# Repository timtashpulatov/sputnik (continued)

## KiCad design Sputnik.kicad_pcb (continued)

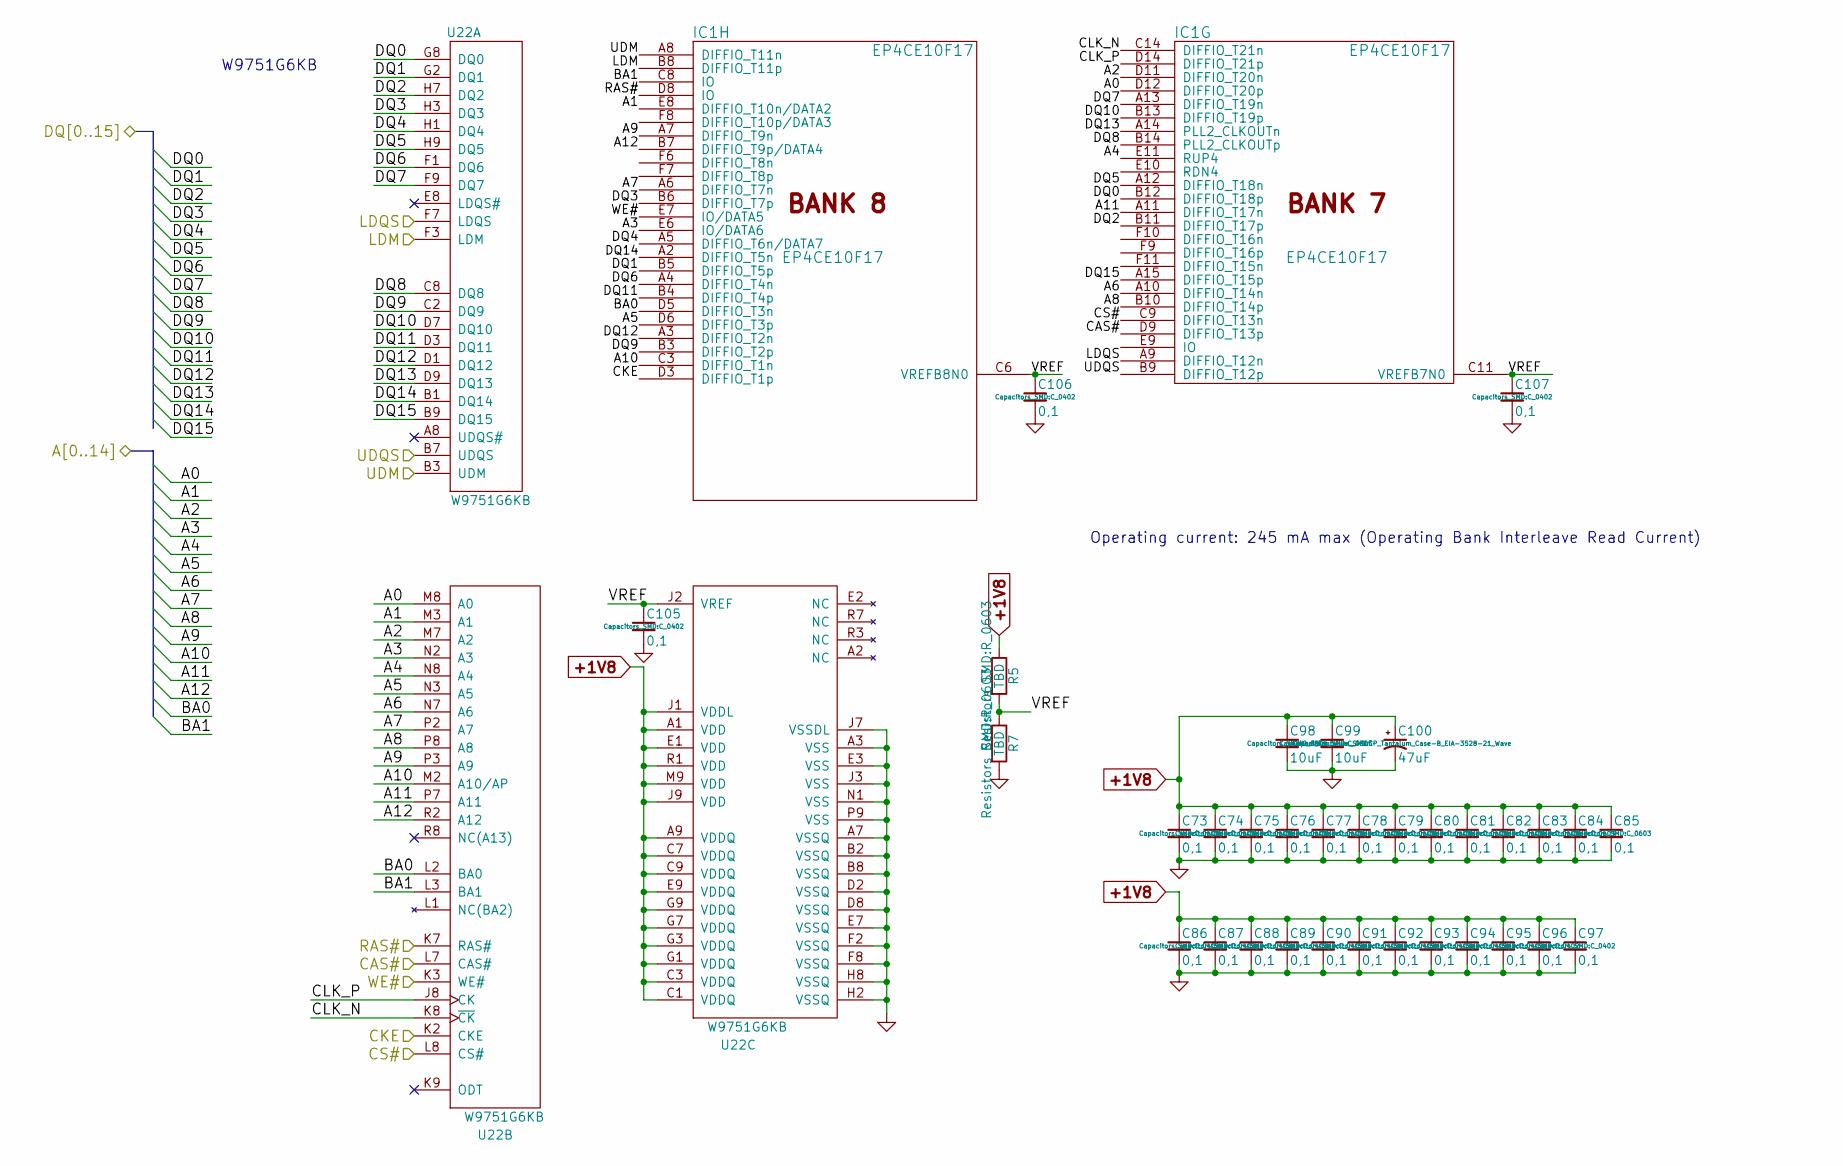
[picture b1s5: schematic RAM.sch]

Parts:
C73, C74, C75, C76, C77, C78, C79, C80, C81, C82, C83, C84, C85: 0,1; C_0603
C86, C87, C88, C89, C90, C91, C92, C93, C94, C95, C96, C97, C105, C106, C107: 0,1; C_0402
C98, C99: 10uF; C_0805
C100: 47uF; CP_Tantalum_Case-B_EIA-3528-21_Wave
IC1: EP4CE10F17; BGA-256-NSMD
R5, R7: TBD; R_0603
U22: W9751G6KB; WBGA-84

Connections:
+1V8: C73.1, C74.1, C75.1, C76.1, C77.1, C78.1, C79.1, C80.1, C81.1, C82.1, C83.1, C84.1, C85.1, C86.1, C87.1, C88.1, C89.1, C90.1, C91.1, C92.1, C93.1, C94.1, C95.1, C96.1, C97.1, C98.1, C99.1, C100.1, R5.1, U22.A1 (VDD), U22.A9 (VDDQ), U22.C1 (VDDQ), U22.C3 (VDDQ), U22.C7 (VDDQ), U22.C9 (VDDQ), U22.E1 (VDD), U22.E9 (VDDQ), U22.G1 (VDDQ), U22.G3 (VDDQ), U22.G7 (VDDQ), U22.G9 (VDDQ), U22.J1 (VDDL), U22.J9 (VDD), U22.M9 (VDD), U22.R1 (VDD); also elsewhere on the board
/RAM/A0: IC1.D12 (DIFFIO_T20p), U22.M8 (A0)
/RAM/A1: IC1.E8 (DIFFIO_T10n/DATA2), U22.M3 (A1)
/RAM/A2: IC1.D11 (DIFFIO_T20n), U22.M7 (A2)
/RAM/A3: IC1.E6 (IO/DATA6), U22.N2 (A3)
/RAM/A4: IC1.E11 (RUP4), U22.N8 (A4)
/RAM/A5: IC1.D6 (DIFFIO_T3p), U22.N3 (A5)
/RAM/A6: IC1.A10 (DIFFIO_T14n), U22.N7 (A6)
/RAM/A7: IC1.A6 (DIFFIO_T7n), U22.P2 (A7)
/RAM/A8: IC1.B10 (DIFFIO_T14p), U22.P8 (A8)
/RAM/A9: IC1.A7 (DIFFIO_T9n), U22.P3 (A9)
/RAM/A10: IC1.C3 (DIFFIO_T1n), U22.M2 (A10/AP)
/RAM/A11: IC1.A11 (DIFFIO_T17n), U22.P7 (A11)
/RAM/A12: IC1.B7 (DIFFIO_T9p/DATA4), U22.R2 (A12)
/RAM/BA0: IC1.D5 (DIFFIO_T3n), U22.L2 (BA0)
/RAM/BA1: IC1.C8 (IO), U22.L3 (BA1)
/RAM/CAS#: IC1.D9 (DIFFIO_T13p), U22.L7 (CAS#)
/RAM/CKE: IC1.D3 (DIFFIO_T1p), U22.K2 (CKE)
/RAM/CLK_N: IC1.C14 (DIFFIO_T21n), U22.K8 (~CK)
/RAM/CLK_P: IC1.D14 (DIFFIO_T21p), U22.J8 (CK)
/RAM/CS#: IC1.C9 (DIFFIO_T13n), U22.L8 (CS#)
/RAM/DQ0: IC1.B12 (DIFFIO_T18p), U22.G8 (DQ0)
/RAM/DQ1: IC1.B5 (DIFFIO_T5p), U22.G2 (DQ1)
/RAM/DQ2: IC1.B11 (DIFFIO_T17p), U22.H7 (DQ2)
/RAM/DQ3: IC1.B6 (DIFFIO_T7p), U22.H3 (DQ3)
/RAM/DQ4: IC1.A5 (DIFFIO_T6n/DATA7), U22.H1 (DQ4)
/RAM/DQ5: IC1.A12 (DIFFIO_T18n), U22.H9 (DQ5)
/RAM/DQ6: IC1.A4 (DIFFIO_T4n), U22.F1 (DQ6)
/RAM/DQ7: IC1.A13 (DIFFIO_T19n), U22.F9 (DQ7)
/RAM/DQ8: IC1.B14 (PLL2_CLKOUTp), U22.C8 (DQ8)
/RAM/DQ9: IC1.B3 (DIFFIO_T2p), U22.C2 (DQ9)
/RAM/DQ10: IC1.B13 (DIFFIO_T19p), U22.D7 (DQ10)
/RAM/DQ11: IC1.B4 (DIFFIO_T4p), U22.D3 (DQ11)
/RAM/DQ12: IC1.A3 (DIFFIO_T2n), U22.D1 (DQ12)
/RAM/DQ13: IC1.A14 (PLL2_CLKOUTn), U22.D9 (DQ13)
/RAM/DQ14: IC1.A2 (DIFFIO_T5n), U22.B1 (DQ14)
/RAM/DQ15: IC1.A15 (DIFFIO_T15p), U22.B9 (DQ15)
/RAM/LDM: IC1.B8 (DIFFIO_T11p), U22.F3 (LDM)
/RAM/LDQS: IC1.A9 (DIFFIO_T12n), U22.F7 (LDQS)
/RAM/RAS#: IC1.D8 (IO), U22.K7 (RAS#)
/RAM/UDM: IC1.A8 (DIFFIO_T11n), U22.B3 (UDM)
/RAM/UDQS: IC1.B9 (DIFFIO_T12p), U22.B7 (UDQS)
/RAM/VREF: C105.1, C106.1, C107.1, IC1.C6 (VREFB8N0), IC1.C11 (VREFB7N0), R5.2, R7.1, U22.J2 (VREF)
/RAM/WE#: IC1.E7 (IO/DATA5), U22.K3 (WE#)
GND: C73.2, C74.2, C75.2, C76.2, C77.2, C78.2, C79.2, C80.2, C81.2, C82.2, C83.2, C84.2, C85.2, C86.2, C87.2, C88.2, C89.2, C90.2, C91.2, C92.2, C93.2, C94.2, C95.2, C96.2, C97.2, C98.2, C99.2, C100.2, C105.2, C106.2, C107.2, R7.2, U22.A3 (VSS), U22.A7 (VSSQ), U22.B2 (VSSQ), U22.B8 (VSSQ), U22.D2 (VSSQ), U22.D8 (VSSQ), U22.E3 (VSS), U22.E7 (VSSQ), U22.F2 (VSSQ), U22.F8 (VSSQ), U22.H2 (VSSQ), U22.H8 (VSSQ), U22.J3 (VSS), U22.J7 (VSSDL), U22.N1 (VSS), U22.P9 (VSS); also elsewhere on the board

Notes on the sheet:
W9751G6KB
Operating current: 245 mA max (Operating Bank Interleave Read Current)

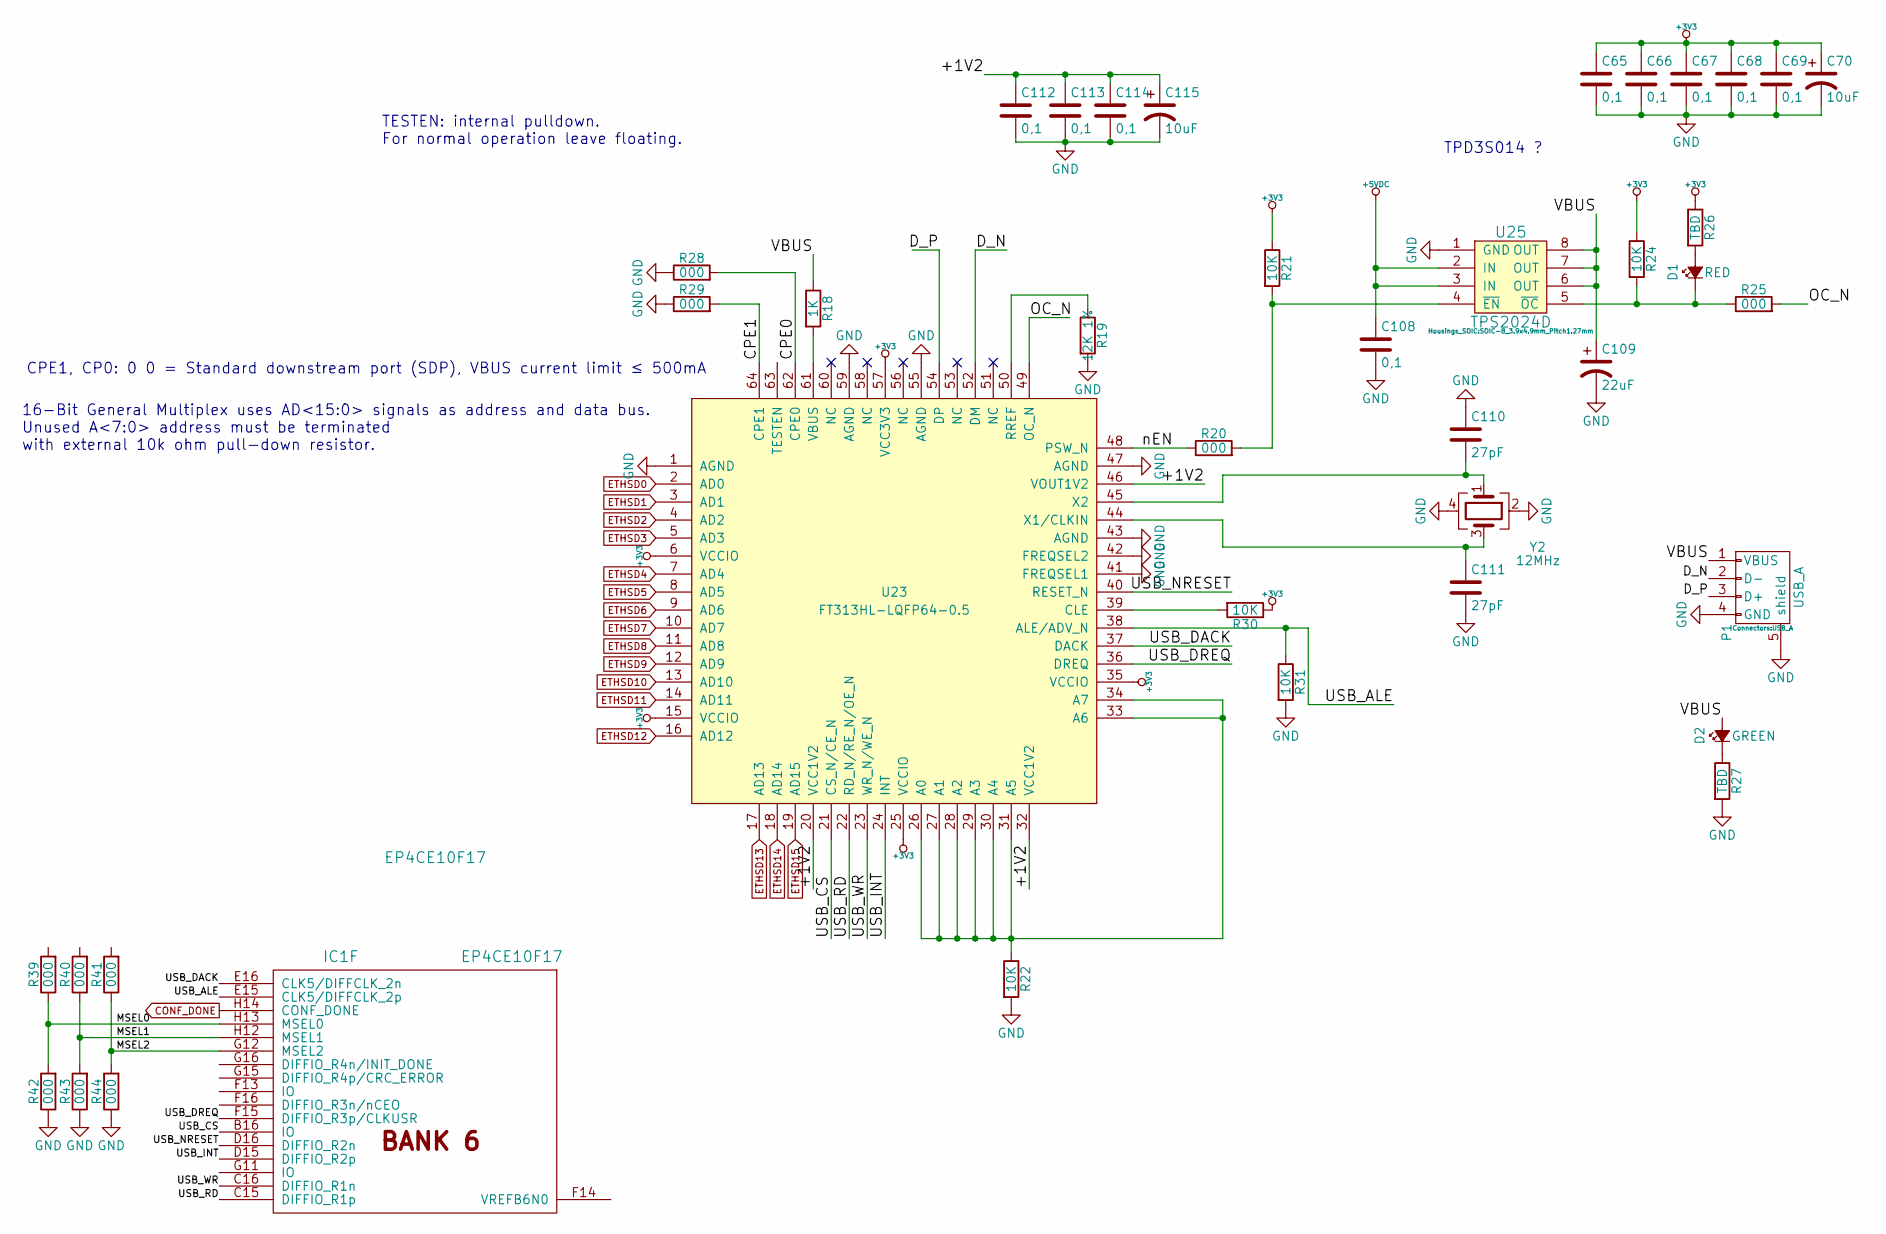
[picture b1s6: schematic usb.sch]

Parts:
C65, C66, C67, C68, C69, C108, C112, C113, C114: 0,1; C_0603
C70, C115: 10uF; CP_Tantalum_Case-B_EIA-3528-21_Reflow
C109: 22uF; CP_Tantalum_Case-C_EIA-6032-28_Reflow
C110, C111: 27pF; C_0603
D1: RED; LED_0603
D2: GREEN; LED_0603
IC1: EP4CE10F17; 256FBGA
P1: USB_A
R18: 1K; R_0603
R19: 12K 1%; R_0603
R20, R25, R28, R29, R39, R40, R41, R42, R43, R44: 000; R_0603
R21, R22, R24, R30, R31: 10K; R_0603
R26, R27: TBD; R_0603
U23: FT313HL-LQFP64-0.5; LQFP-64_10x10mm_Pitch0.5mm
U25: TPS2024D; SOIC-8_3.9x4.9mm_Pitch1.27mm
Y2: 12MHz; Crystal_SMD_3225-4pin_3.2x2.5mm

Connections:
+3V3: C65.1, C66.1, C67.1, C68.1, C69.1, C70.1, R21.1, R24.1, R26.1, R30.1, U23.6 (VCCIO), U23.15 (VCCIO), U23.25 (VCCIO), U23.35 (VCCIO), U23.57 (VCC3V3); also elsewhere on the board
+5VDC: C108.1, U25.2 (IN), U25.3 (IN); also elsewhere on the board
/usb/+1V2: C112.1, C113.1, C114.1, C115.1, U23.20 (VCC1V2), U23.32 (VCC1V2), U23.46 (VOUT1V2)
/usb/CPE0: R28.2, U23.62 (CPE0)
/usb/CPE1: R29.2, U23.64 (CPE1)
/usb/D_N: P1.2 (D-), U23.52 (DM)
/usb/D_P: P1.3 (D+), U23.54 (DP)
/usb/MSEL0: IC1.H13 (MSEL0), R39.1, R42.2
/usb/MSEL1: IC1.H12 (MSEL1), R40.1, R43.2
/usb/MSEL2: IC1.G12 (MSEL2), R41.1, R44.2
/usb/OC_N: R25.2, U23.49 (OC_N)
/usb/USB_ALE: IC1.E15 (CLK5/DIFFCLK_2p), R31.1, U23.38 (ALE/ADV_N)
/usb/USB_CS: IC1.B16 (IO), U23.21 (CS_N/CE_N)
/usb/USB_DACK: IC1.E16 (CLK5/DIFFCLK_2n), U23.37 (DACK)
/usb/USB_DREQ: IC1.F15 (DIFFIO_R3p/CLKUSR), U23.36 (DREQ)
/usb/USB_INT: IC1.D15 (DIFFIO_R2p), U23.24 (INT)
/usb/USB_NRESET: IC1.D16 (DIFFIO_R2n), U23.40 (RESET_N)
/usb/USB_RD: IC1.C15 (DIFFIO_R1p), U23.22 (RD_N/RE_N/OE_N)
/usb/USB_WR: IC1.C16 (DIFFIO_R1n), U23.23 (WR_N/WE_N)
/usb/VBUS: C109.1, D2.2 (A), P1.1 (VBUS), R18.1, U25.6 (OUT), U25.7 (OUT), U25.8 (OUT)
/usb/nEN: R20.1, U23.48 (PSW_N)
CONF_DONE: IC1.H14 (CONF_DONE); also elsewhere on the board
ETHSD0: U23.2 (AD0); also elsewhere on the board
ETHSD1: U23.3 (AD1); also elsewhere on the board
ETHSD2: U23.4 (AD2); also elsewhere on the board
ETHSD3: U23.5 (AD3); also elsewhere on the board
ETHSD4: U23.7 (AD4); also elsewhere on the board
ETHSD5: U23.8 (AD5); also elsewhere on the board
ETHSD6: U23.9 (AD6); also elsewhere on the board
ETHSD7: U23.10 (AD7); also elsewhere on the board
ETHSD8: U23.11 (AD8); also elsewhere on the board
ETHSD9: U23.12 (AD9); also elsewhere on the board
ETHSD10: U23.13 (AD10); also elsewhere on the board
ETHSD11: U23.14 (AD11); also elsewhere on the board
ETHSD12: U23.16 (AD12); also elsewhere on the board
ETHSD13: U23.17 (AD13); also elsewhere on the board
ETHSD14: U23.18 (AD14); also elsewhere on the board
ETHSD15: U23.19 (AD15); also elsewhere on the board
GND: C65.2, C66.2, C67.2, C68.2, C69.2, C70.2, C108.2, C109.2, C110.1, C111.2, C112.2, C113.2, C114.2, C115.2, P1.4 (GND), P1.5 (shield), R19.2, R22.2, R27.2, R28.1, R29.1, R31.2, R42.1, R43.1, R44.1, U23.1 (AGND), U23.41 (FREQSEL1), U23.42 (FREQSEL2), U23.43 (AGND), U23.47 (AGND), U23.55 (AGND), U23.59 (AGND), U25.1 (GND), Y2.2, Y2.4; also elsewhere on the board
unnamed: C110.2, U23.45 (X2), Y2.1
unnamed: C111.1, U23.44 (X1/CLKIN), Y2.3
unnamed: D1.1 (K), R24.2, R25.1, U25.5 (~OC)
unnamed: D1.2 (A), R26.2
unnamed: D2.1 (K), R27.1
unnamed: R18.2, U23.61 (VBUS)
unnamed: R19.1, U23.50 (RREF)
unnamed: R20.2, R21.2, U25.4 (~EN)
unnamed: R22.1, U23.26 (A0), U23.27 (A1), U23.28 (A2), U23.29 (A3), U23.30 (A4), U23.31 (A5), U23.33 (A6), U23.34 (A7)
unnamed: R30.2, U23.39 (CLE)

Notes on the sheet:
TESTEN: internal pulldown. For normal operation leave floating.
CPE1, CP0: 0 0 = Standard downstream port (SDP), VBUS current limit ≤ 500mA
16-Bit General Multiplex uses AD<15:0> signals as address and data bus. Unused A<7:0> address must be terminated with external 10k ohm pull-down resistor.
TPD3S014 ?

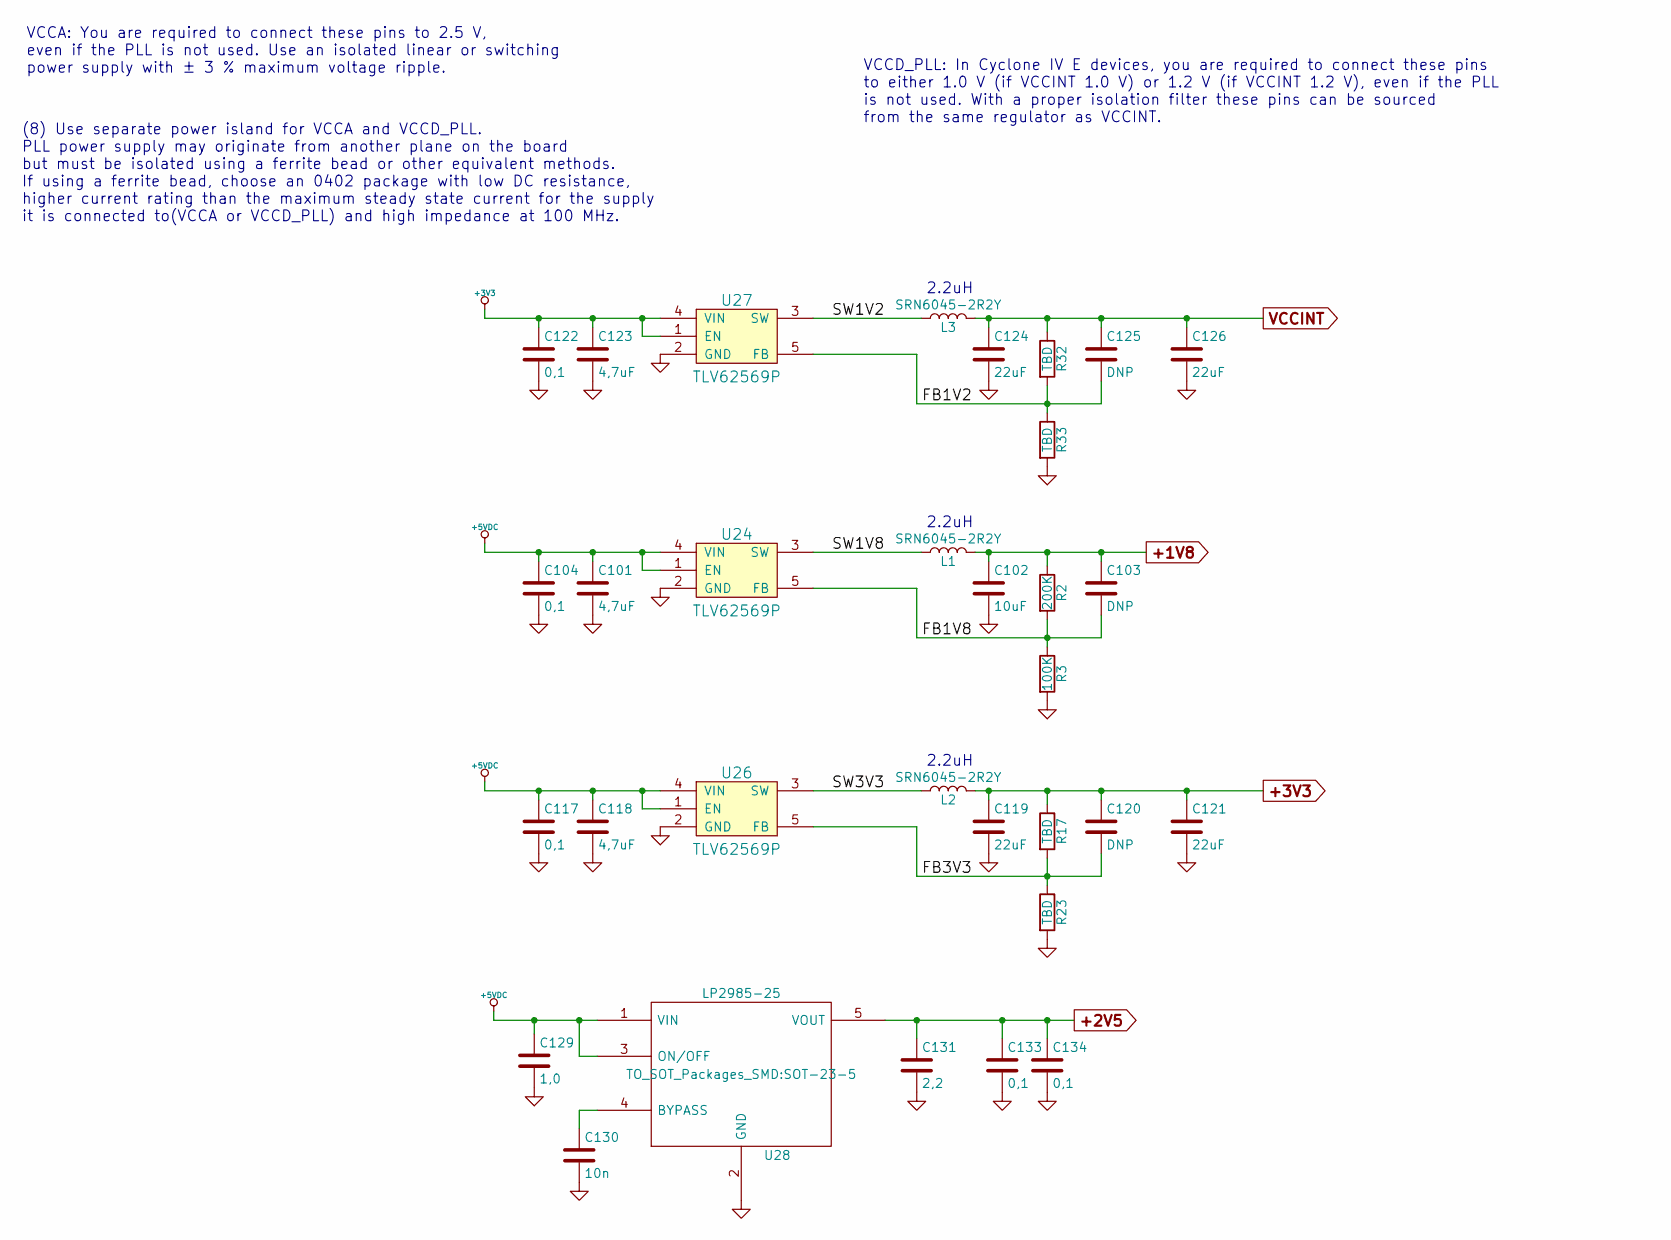
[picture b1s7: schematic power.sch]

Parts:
C101, C118, C123: 4,7uF; C_0805
C102: 10uF; C_0805
C103, C120, C125: DNP; C_0603
C104, C117, C122: 0,1; C_0603
C119, C121, C124, C126: 22uF; CP_Tantalum_Case-B_EIA-3528-21_Reflow
C129: 1,0; C_0805
C130: 10n; C_0603
C131: 2,2; C_0805
C133, C134: 0,1; C_0402
L1, L2, L3: SRN6045-2R2Y; SRN6045
R2: 200K; R_0603
R3: 100K; R_0603
R17, R23, R32, R33: TBD; R_0603
U24, U26, U27: TLV62569P; SOT-23-5
U28: LP2985-25; SOT-23-5

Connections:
+1V8: C102.1, C103.1, L1.2, R2.1; also elsewhere on the board
+2V5: C131.1, C133.1, C134.1, U28.5 (VOUT); also elsewhere on the board
+3V3: C119.1, C120.1, C121.1, C122.1, C123.1, L2.2, R17.1, U27.1 (EN), U27.4 (VIN); also elsewhere on the board
+5VDC: C101.1, C104.1, C117.1, C118.1, C129.1, U24.1 (EN), U24.4 (VIN), U26.1 (EN), U26.4 (VIN), U28.1 (VIN), U28.3 (ON/OFF); also elsewhere on the board
/Power/FB1V2: C125.2, R32.2, R33.1, U27.5 (FB)
/Power/FB1V8: C103.2, R2.2, R3.1, U24.5 (FB)
/Power/FB3V3: C120.2, R17.2, R23.1, U26.5 (FB)
/Power/SW1V2: L3.1, U27.3 (SW)
/Power/SW1V8: L1.1, U24.3 (SW)
/Power/SW3V3: L2.1, U26.3 (SW)
GND: C101.2, C102.2, C104.2, C117.2, C118.2, C119.2, C121.2, C122.2, C123.2, C124.2, C126.2, C129.2, C130.2, C131.2, C133.2, C134.2, R3.2, R23.2, R33.2, U24.2 (GND), U26.2 (GND), U27.2 (GND), U28.2 (GND); also elsewhere on the board
unnamed: C130.1, U28.4 (BYPASS)
VCCINT: C124.1, C125.1, C126.1, L3.2, R32.1; also elsewhere on the board

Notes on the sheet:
2.2uH
VCCA: You are required to connect these pins to 2.5 V, even if the PLL is not used. Use an isolated linear or switching power supply with ± 3 % maximum voltage ripple.
(8) Use separate power island for VCCA and VCCD_PLL. PLL power supply may originate from another plane on the board but must be isolated using a ferrite bead or other equivalent methods. If using a ferrite bead, choose an 0402 package with low DC resistance, higher current rating than the maximum s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
VCCD_PLL: In Cyclone IV E devices, you are required to connect these pins to either 1.0 V (if VCCINT 1.0 V) or 1.2 V (if VCCINT 1.2 V), even if the PLL is not used. With a proper isolation filter these pins can be sourced from the same regulator as VCCINT.

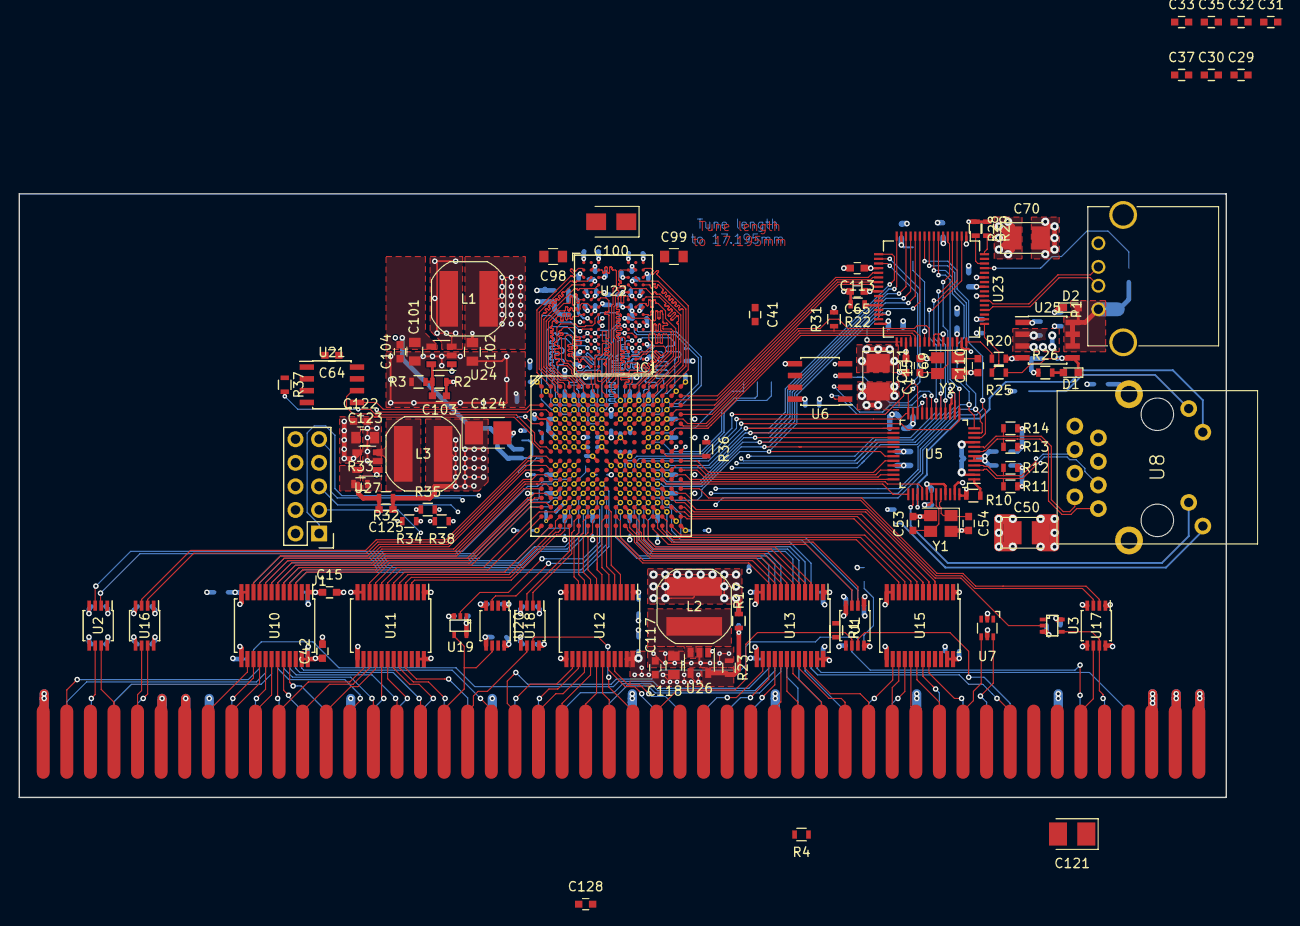
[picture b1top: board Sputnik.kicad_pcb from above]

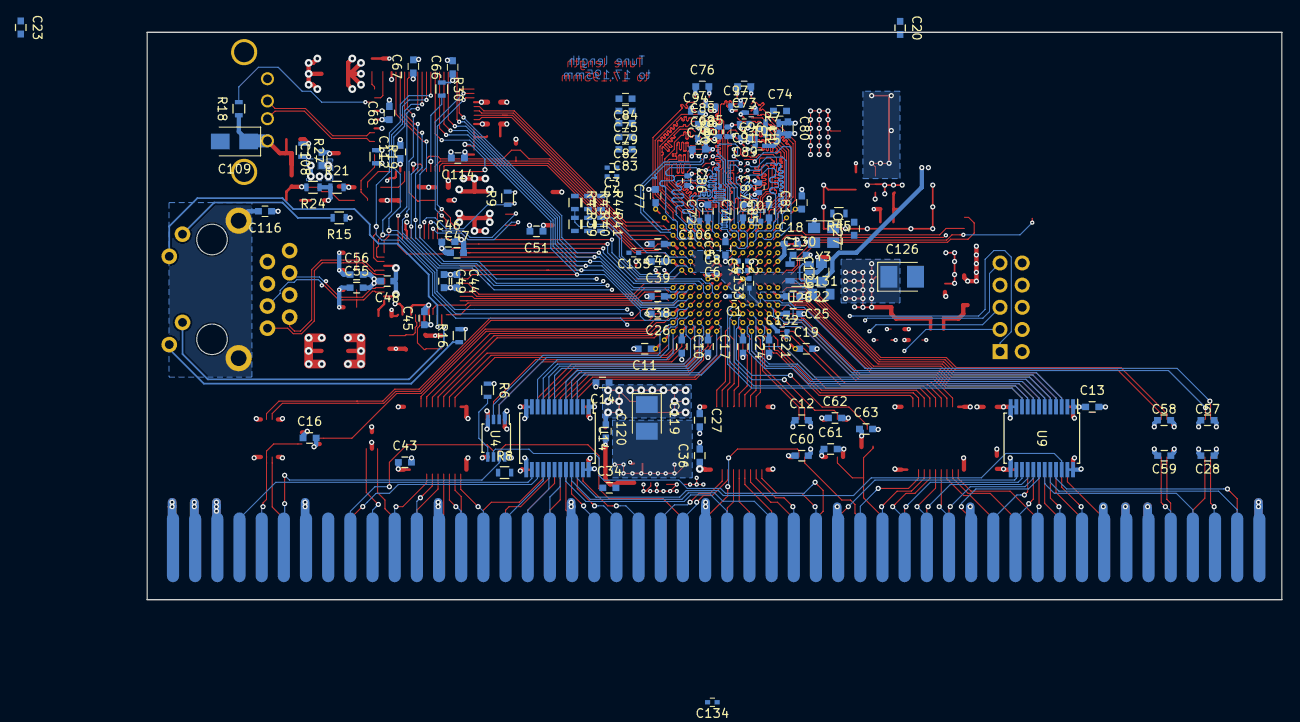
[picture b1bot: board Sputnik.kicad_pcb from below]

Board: 4 copper layers, 130.0 x 65.0 mm, 218 parts (122 on the bottom side), 285 nets.

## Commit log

2016-10-22 Initial
2016-10-22 Add .gitignore
2016-10-22 Add most files
2016-10-22 Rename dm9k.pdf
2016-10-22 Lib: 93lc46
2016-10-22 Add dm9k schematics
2016-10-22 Pulse jack added
2016-10-30 More docs
2016-10-30 Even more docs
2016-10-30 Sch/pcb update
2016-11-07 Docs added
2016-11-10 SD lines rearranged
2016-11-11 More 5V signals rearranged
2016-11-11 Add SN74LVC2T45
2016-11-13 Massive board changes
2016-11-13 Moar
2016-11-13 PCB updates
2016-11-14 Swapping signals
2016-11-14 Swapping, bottom side
2016-11-16 Bottom PCB routing
2016-11-16 Open drain signals
2016-11-17 More routing
2016-11-17 Still routing
2016-12-13 And more
2016-12-19 KEL connector datasheet and footprints
2016-12-20 More routing and caps
2016-12-21 Added nMTACK and nCINH signals
2016-12-21 Squeezed nBG and E_CLOCK as well
2016-12-21 nDTACK* rerouted
2016-12-21 nCFGINn and nSLAVEn routed
2016-12-26 Moved RJ45 socket, adjusted inner +3V3 copper pour
2016-12-26 Lotta changes
2016-12-26 Routing dm9000 lines
2016-12-26 Inner layers routing
2016-12-27 Ethernet SD bus resolved
2016-12-27 More eth stuff
2017-01-12 Added FT313H
2017-01-12 Added USB sheet
2017-01-12 FT313 fitting
2017-01-14 More USB signals
2017-01-20 Added Winbond DDR2 chip
2017-01-20 Start fitting DDR2
2017-01-21 DDR signals assignment and routing in progress
2017-01-21 DDR bottom signals length matched
2017-01-22 Bottom 1V8 caps in progress
2017-01-22 DDR2 bottom decoupling
2017-01-22 More bottom length matching
2017-01-23 Even more track length tuning
2017-01-23 DDR clock redone
2017-01-25 Cleanups
2017-01-25 More tuning
2017-01-25 Up..
2017-01-25 More tuning...
2017-01-26 1V8 caps added, bit of routing
2017-01-27 Added power sheet, 1V8 chip docs etc
2017-01-27 More 1V8 stuff
2017-01-28 Update 1V8 PSU
2017-01-28 VREF for DDR2
2017-01-28 VREF18 for FPGA WIP
2017-01-30 More caps for VREF
2017-01-30 More caps for VREF-2
2017-01-30 Add USB connector
2017-01-31 More USB stuff
2017-02-01 A bit of routing
2017-02-02 USB/Ethernet AD tracks swapped and routed
2017-02-02 Crystals fix, USB rearranged
2017-02-04 Added VBUS and OC LEDs
2017-02-04 USB stuff update
2017-02-05 Add CPEx config resistors
2017-02-06 ALE and CLE routed
2017-02-06 FREQSEL eliminated
2017-02-06 FT313 unused A0..A7 lines tied to GND
2017-02-09 Shield copper pour for RJ45
2017-02-09 TX/RX pairs routed
2017-02-14 +5V routing
2017-02-14 More PCB work
2017-02-15 PCB rework, JTAG connector moved, VREF routed
2017-02-16 Top tracks cleanup
2017-02-16 JTAG connections
2017-02-16 +3V3 PSU
2017-02-16 +3V3 placement and early routing
2017-02-16 Another up
2017-02-18 Added VCCINT power supply
2017-02-18 Add KXO-V97 footprint
2017-02-20 A bit of update
2017-02-20 VCCA and VCCD_PLL
2017-02-27 VCCA added
2017-02-27 VCCD_PLL routed
2017-03-02 CONF_DONE and MSELx routed
2017-03-02 JTAG and +2V5 work in progress
2017-03-10 EPCS lines routed
2017-03-25 Bit of +2V5 routing
2017-03-26 More PCB routin
